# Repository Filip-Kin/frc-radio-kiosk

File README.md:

# FRC radio kiosk

Bench box that powers and configures FRC radios: dual-mode PoE (802.3at via
LTC4279, passive 12 V via TPS26600), USB-C PD or DC in, 15.6 V out for the
Toughbook, 4x CR123A backup, STM32F072 firmware.

- `Radio_Kiosk_v2/` first full board, 100 x 130 mm
- `Radio_Kiosk_v2b/` hand-packed board, 84 x 133 mm, 2 oz copper (order that at JLC)
- `Radio_Kiosk_v2d/` 4-layer rework of v2c, 85 x 120 mm, In1 GND plane (see its NOTES.md)
- `Radio_Kiosk_v1/` the built board, 70 x 105 mm: USB-C PD 20 V in, XL4015 16 V laptop out, LM2596 12 V passive PoE. Board was drawn in EasyEDA Pro; `fab/` is its 2026-03-25 export (Gerbers, BOM, STEP, 3D shell). The KiCad schematic is an early draft, not the built circuit.
- each board dir: `board.kicad_sch`, `board.kicad_pcb`, `board.kicad_pro`, `board.loon.json`, `firmware/` (PlatformIO)

The schematic and board are generated by scripts in
[loon](https://github.com/Filip-Kin/loon): `scripts/build-radio-kiosk.ts`,
`build-radio-kiosk-pcb.ts` (v2), `build-radio-kiosk-pcb-v2b.ts`. Design notes
are on the internal wiki (`frc/radio-kiosk-pcb`).

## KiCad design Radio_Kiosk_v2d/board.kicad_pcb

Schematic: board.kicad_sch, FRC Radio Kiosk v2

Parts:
BT1, BT2, BT3, BT4: CR123A; BAT-TH_BH-123A-A5BJ002; LCSC C5290177
C1, C2, C6, C7, C12, C13, C16, C17, C33, C48, C53, C99, C110, C111, C112, C114, C115, C116, C120, C131, C132, C133, C136: 100n; C_0805_2012Metric; LCSC C28233
C3, C5: 100n/50V; C_0805_2012Metric; LCSC C49678
C4: 47u/63V; CP_Elec_8x10.5; LCSC C970680
C8, C61, C140: 1u/50V; C_1206_3216Metric; LCSC C1848
C14, C15, C113, C135: 10n; C_0805_2012Metric; LCSC C1710
C20: 100p; C_0805_2012Metric; LCSC C1790
C21, C60, C119: 47n; C_0805_2012Metric; LCSC C53134
C22: 10u/25V; C_1210_3225Metric; LCSC C53084452
C23, C24, C26: 4.7u/100V; C_1210_3225Metric; LCSC C337978
C25: 47u/100V; CP_Elec_10x10.5; LCSC C970681
C30, C40, C44, C50, C90, C91: 10u/50V; C_1210_3225Metric; LCSC C53084452
C31, C41, C51: 220n/50V; C_0805_2012Metric; LCSC C5378
C32, C52, C118, C134: 1u; C_0805_2012Metric; LCSC C28323
C34, C35, C36, C37, C45, C54, C55, C56, C57: 22u/25V; C_1210_3225Metric; LCSC C53084530
C42: 4.7u/16V; C_0805_2012Metric; LCSC C1779
C43: 470n/16V; C_0805_2012Metric; LCSC C13967
C46: 220u/25V polymer; CP_Elec_6.3x7.7; LCSC C2981459
C49: 2.2n; C_0805_2012Metric; LCSC C28260
C62, C70: 1u/100V; C_1210_3225Metric; LCSC C24365
C71: 220n/100V; C_1210_3225Metric; LCSC C72067
C97, C98: 470u/25V; CP_Elec_10x10.5; LCSC C346948
C117: 4.7n; C_0805_2012Metric; LCSC C1744
C130: 4.7u; C_0805_2012Metric; LCSC C1779
C141: 1u; C_0603_1608Metric; LCSC C15849
C142, C143: 10u; C_0603_1608Metric; LCSC C19702
D1: SMAJ22A TVS; D_SMA; LCSC C148220
D2: SMAJ28A TVS; D_SMA; LCSC C148227
D20: SS310 100V Schottky; D_SMA; LCSC C15874
D21, D40: 1N4148W; D_SOD-123; LCSC C81598
D22, D70: SMAJ58A TVS; D_SMA; LCSC C10762
D23, D24: BZT52C12 zener; D_SOD-123; LCSC C12747
D30: WS2812B-4020 power LED; LED-SMD_WS2812B-4020; LCSC C965557
D31: WS2812B-4020 radio LED; LED-SMD_WS2812B-4020; LCSC C965557
D32: SS14 flyback; D_SMA; LCSC C2480
D71: S1B clamp; D_SMA; LCSC C96324
F1: 2A; Fuse_1206_3216Metric; LCSC C2838912
J1: USB-C PD in; USB-C_TYPE-C-31-M-12; LCSC C165948
J2: DC in 18-26V, PJ-002BH 5.5x2.5; DC-IN-TH_PJ-002BH; LCSC C22359705
J3: Laptop out 15.6V, PJ-002BH 5.5x2.5 (v1 jack); DC-IN-TH_PJ-002BH; LCSC C22359705
J5: RJ45 radio; RJ45-TH_R-RJ45R08P-A004; LCSC C385834
J6: RJ45 laptop; RJ45-TH_R-RJ45R08P-A004; LCSC C385834
J8: Fan 12V; CONN-TH_XH-2A; LCSC C20079
J9: SWD; PinHeader_1x04_P2.54mm_Vertical
J11: UART; PinHeader_1x04_P2.54mm_Vertical
J12: USB-C; USB_C_Receptacle_HRO_TYPE-C-31-M-12; LCSC C165948
J13: Lid LEDs; CONN-TH_XH-3A; LCSC C2316
L3, L4: MDA1040-150M 15u 6A; IND-SMD_L10.0-W10.0-APS10A40M470; LCSC C2847554
L5: SRP7028A-100M 10u 3.5A; L_Bourns_SRP7028A_7.3x6.6mm; LCSC C2687402
L20: MDA1365-330M 33u 9A; L_12x12mm_H8mm; LCSC C2847586
Q1, Q2, Q6, Q7, Q12: SI4470EY; SOIC-8_3.9x4.9mm_P1.27mm; LCSC C7568913
Q8: AOD4185; TO-252-2; LCSC C400894
Q9, Q10, Q25, Q45: 2N7002; SOT-23; LCSC C8545
Q11, Q30: AO3400A; SOT-23; LCSC C20917
Q13, Q20: AO4482; SOIC-8_3.9x4.9mm_P1.27mm; LCSC C192576
Q22: PSMN075-100MSEX; LFPAK33; LCSC C478016
Q23: DMP10H400SE; SOT-223_L6.5-W3.5-P2.30-LS7.0-BR; LCSC C156277
Q24: BSS123; SOT-23; LCSC C78755
Q40, Q41: AOD4184A; TO-252-2; LCSC C99124
Q44: SI4401DDY; SOIC-8_3.9x4.9mm_P1.27mm; LCSC C72317
R5, R6, R29, R42, R80, R89, R92, R97, R100, R101: 100k; R_0805_2012Metric; LCSC C149504
R7, R9, R24, R26, R27, R46, R47, R49, R61, R62, R63, R66, R78, R79, R82, R83, R99, R105, R107, R111, R121: 10k; R_0805_2012Metric; LCSC C17414
R8, R21, R28, R48: 47k; R_0805_2012Metric; LCSC C17713
R10, R31: 20k; R_0805_2012Metric; LCSC C4328
R20: 15m 1W; R_2512_6332Metric; LCSC C44883
R22: 499k 1%; R_0805_2012Metric; LCSC C17721
R23, R50: 12k; R_0805_2012Metric; LCSC C17444
R25, R81: 1k; R_0805_2012Metric; LCSC C17513
R30: 220k; R_0805_2012Metric; LCSC C17556
R40: 2k; R_0805_2012Metric; LCSC C17604
R41, R65: 51k; R_0805_2012Metric; LCSC C17737
R44: 820k; R_0805_2012Metric; LCSC C50136
R45: 750R; R_0805_2012Metric; LCSC C17818
R51: 3k; R_0805_2012Metric; LCSC C17661
R60: 5.6k; R_0805_2012Metric; LCSC C4382
R64, R86: 1M 1%; R_0805_2012Metric; LCSC C17514
R70: 10R; R_0805_2012Metric; LCSC C17415
R71: 200R; R_0805_2012Metric; LCSC C17540
R72: 0.1R 1% 2W; R_2512_6332Metric; LCSC C844904
R73: 3.3k; R_0805_2012Metric; LCSC C26010
R74, R75, R76, R77, R103, R106: 100R; R_0805_2012Metric; LCSC C17408
R84: 1M; R_0805_2012Metric; LCSC C17514
R85, R88: 24R 2W pulse; R_2512_6332Metric; LCSC C25476
R87: 150k; R_0805_2012Metric; LCSC C17470
R90, R94: 33k; R_0805_2012Metric; LCSC C17633
R91, R95, R98: 4.7k; R_0805_2012Metric; LCSC C17673
R93, R96: 20m 1W; R_2512_6332Metric; LCSC C2885416
R104: 1R; R_0805_2012Metric; LCSC C25271
R112: 0R; R_0805_2012Metric; LCSC C17477
R113: 220R; R_0805_2012Metric; LCSC C17557
R120: 120k 1%; R_0805_2012Metric; LCSC C17436
R122, R123: 5.1k; R_0603_1608Metric; LCSC C23186
RT1: 10k NTC; R_0603_1608Metric; LCSC C13564
SW1: RESET; SW_SPST_B3U-1000P; LCSC C231329
SW2: BOOT0 (DFU); SW_SPST_B3U-1000P; LCSC C231329
U1, U2, U6, U7, U12: LM74700-Q1; SOT-23-6; LCSC C2941042
U3: LMR33630 12V; SOIC-8-1EP_3.9x4.9mm_P1.27mm_EP2.29x3mm; LCSC C841384
U4: LM3150 15.75V 4.5A; HTSSOP-14_L5.0-W4.4-P0.65-LS6.4-BL-EP; LCSC C48112
U5: LMR33630 5V; SOIC-8-1EP_3.9x4.9mm_P1.27mm_EP2.29x3mm; LCSC C841384
U10, U45: TLV7011; SOT-23-5; LCSC C702117
U20: LM3478 54V boost; SOIC-8_3.9x4.9mm_P1.27mm; LCSC C115907
U21: TPS26600 eFuse; HTSSOP-16-1EP_4.4x5mm_P0.65mm_EP3.4x5mm; LCSC C544399
U22: LTC4279; SOIC-16_3.9x9.9mm_P1.27mm; LCSC C687935
U30, U31: SN74AHCT1G125; SOT-23-5; LCSC C7484
U40: STM32F072CBT6; LQFP-48_7x7mm_P0.5mm; LCSC C81720
U41, U42: INA180A1; SOT-23-5; LCSC C122228
U43: MCP6001T-I/OT; SOT-23-5; LCSC C116490
U50: CH224A; ESSOP-10_CH224A; LCSC C42459160
U51: AP2112K-3.3; SOT-23-5; LCSC C51118
U52: USBLC6-2SC6; SOT-23-6; LCSC C7519

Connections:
+3V3: C17.1, C99.1, C115.1, C116.1, C120.1, C130.1, C131.1, C132.1, C133.1, C142.1, J9.3, J11.3, R26.1, R62.1, R79.1, R82.1, R107.1, R112.1, R121.1, SW2.2, U10.5 (VCC), U40.1 (VBAT), U40.24 (VDD), U40.36 (VDDIO2), U40.48 (VDD), U41.5 (VS), U42.5 (VS), U43.5 (VDD), U45.5 (VCC), U51.5 (VOUT)
+5V: C16.1, C54.1, C55.1, C56.1, C57.1, C110.1, C111.1, C112.1, C141.1, D30.2 (VDD), D31.2 (VDD), J13.1 (5V), L5.2, R50.1, U30.5 (VCC), U31.5 (VCC), U51.1 (VIN), U51.3 (EN)
+12V: C22.1, C50.1, C51.1, C61.1, C97.1, C98.1, D32.1 (K), J8.1, L20.1, Q6.5 (D), Q6.6 (D), Q6.7 (D), Q6.8 (D), Q8.2 (D), U5.2 (VIN), U5.3 (EN), U6.4 (CATHODE), U20.8 (VIN), U21.1 (IN), U21.2 (IN), U21.3 (UVLO)
+12V_BUCK: C6.2, C34.1, C35.1, C36.1, C37.1, L3.2, Q6.1 (S), Q6.2 (S), Q6.3 (S), R30.1, U6.3 (EN), U6.6 (ANODE)
+15V6_BUCK: C45.1, C46.1, C49.1, L4.2, R41.1, R96.1, U42.3 (IN+)
+15V6_S: C5.1, C7.2, Q7.1 (S), Q7.2 (S), Q7.3 (S), Q44.5 (D), Q44.6 (D), Q44.7 (D), Q44.8 (D), R96.2, U7.3 (EN), U7.6 (ANODE), U42.4 (IN-)
BK_ARM: Q9.2 (S), Q10.3 (D)
BK_DRV: Q9.1 (G), R81.2
BK_EN: Q10.1 (G), R89.1, U12.3 (EN), U40.5 (PF0/OSC_IN)
BK_GATE: Q8.1 (G), Q9.3 (D), R80.2
BK_MID: Q8.3 (S), Q12.5 (D), Q12.6 (D), Q12.7 (D), Q12.8 (D), R80.1, R85.1, R86.1, R88.1, U12.4 (CATHODE)
BK_ON: R81.1, R84.1, U10.1 (OUT), U40.6 (PF1/OSC_OUT)
BK_REF: R82.2, R83.1, R84.2, U10.3 (IN+)
BOOST_COMP: R24.1, U20.2 (COMP)
BOOST_COMPC: C21.1, R24.2
BOOST_CS: Q20.1 (S), Q20.2 (S), Q20.3 (S), R20.1, U20.1 (ISEN)
BOOST_DR: Q20.4 (G), U20.6 (DR)
BOOST_FA: D21.1 (K), R21.1, U20.7 (FA/SD)
BOOST_FB: C20.1, R22.2, R23.1, U20.3 (FB)
BOOST_OUT: C23.1, C24.1, C25.1, C26.1, D20.1 (K), D23.1 (K), Q23.3 (S), R22.1, R27.1, R42.1
BOOST_SD: R25.1, R26.2, U40.27 (PB14)
BOOST_SDD: D21.2 (A), R25.2
BOOST_SW: D20.2 (A), L20.2, Q20.5 (D), Q20.6 (D), Q20.7 (D), Q20.8 (D)
BYP_D: Q45.3 (D), R8.2
BYP_EN: Q45.1 (G), U45.1 (OUT)
BYP_G: D24.2 (A), Q44.4 (G), R7.2, R8.1
BYP_REF: R9.2, R10.1, U45.3 (IN+)
CC1: J12.A5 (CC1), R122.1
CC2: J12.B5 (CC2), R123.1
DCIN_SENSE: R94.2, R95.1, U40.19 (PB1/ADC9)
ETH_1: J5.1, J6.1
ETH_2: J5.2, J6.2
ETH_3: J5.3, J6.3
ETH_6: J5.6, J6.6
FAN_G: Q30.1 (G), R101.1, R106.2
FAN_N: D32.2 (A), J8.2, Q30.3 (D)
FAN_PWM: R106.1, U40.40 (PB4)
FAN_SENSE: C113.1, R105.2, U40.18 (PB0/ADC8)
FAN_SHUNT: Q30.2 (S), R104.1, R105.1
GND: BT4.2 (-), C3.2, C4.2, C5.2, C8.2, C13.2, C14.2, C15.2, C16.2, C17.2, C20.2, C21.2, C22.2, C23.2, C24.2, C25.2, C26.2, C30.2, C31.2, C32.2, C34.2, C35.2, C36.2, C37.2, C40.2, C41.2, C42.2, C44.2, C45.2, C46.2, C48.2, C50.2, C51.2, C52.2, C54.2, C55.2, C56.2, C57.2, C60.2, C61.2, C62.2, C70.2, C90.2, C91.2, C97.2, C98.2, C99.2, C110.2, C111.2, C112.2, C113.2, C114.2, C115.2, C116.2, C118.2, C119.2, C120.2, C130.2, C131.2, C132.2, C133.2, C134.2, C135.2, C136.2, C140.2, C141.2, C142.2, C143.2, D1.2 (A), D2.2 (A), D22.2 (A), D30.4 (VSS), D31.4 (VSS), D70.2 (A), J1.1 (SHELL), J1.2 (SHELL), J1.3 (SHELL), J1.4 (SHELL), J1.A1B12 (GND), J1.B1A12 (GND), J2.2 (GND), J3.2 (GND), J9.4, J11.4, J12.A1 (GND), J12.A12, J12.B1 (GND2), J12.B12, J12.S1 (SHIELD), J13.3 (GND), Q10.2 (S), Q11.2 (S), Q13.1 (S), Q13.2 (S), Q13.3 (S), Q24.2 (S), Q25.2 (S), Q41.3 (S), Q45.2 (S), R6.2, R10.2, R20.2, R21.2, R23.2, R29.2, R31.2, R40.2, R42.2, R49.2, R51.2, R60.2, R61.2, R63.2, R65.2, R66.2, R72.2, R73.2, R74.2, R75.2, R76.2, R78.2, R83.2, R87.2, R89.2, R91.2, R92.2, R95.2, R100.2, R101.2, R104.2, R111.2, R120.2, R122.2, R123.2, RT1.2, SW1.2, U1.2 (GND), U2.2 (GND), U3.1 (PGND), U3.9 (AGND), U4.5 (SGND), U4.9 (SGND), U4.14 (PGND), U4.15 (EP), U5.1 (PGND), U5.9 (AGND), U6.2 (GND), U7.2 (GND), U10.2 (VEE), U12.2 (GND), U20.4 (AGND), U20.5 (PGND), U21.5 (OVP), U21.8 (RTN), U21.9 (GND), U21.17 (PAD), U22.4 (VSSK), U22.10 (VEE), U30.1 (OE), U30.3 (GND), U31.1 (OE), U31.3 (GND), U40.8 (VSSA), U40.23 (VSS), U40.35 (VSS), U40.47 (VSS), U41.2 (GND), U42.2 (GND), U43.2 (VSS), U45.2 (VEE), U50.11 (EPAD), U51.2 (GND), U52.2 (GND)
LAPTOP_BYP: R9.1, U40.20 (PB2)
LAPTOP_CC: C117.1, D40.2 (A), U43.1 (OUT)
LAPTOP_CC_D: D40.1 (K), R98.1
LAPTOP_EN: R46.1, U40.46 (PB9)
LAPTOP_ILIM: C118.1, R97.1, R99.2
LAPTOP_ILIM_N: C117.2, R97.2, U43.4 (IN-)
LAPTOP_ILIM_PWM: R99.1, U40.29 (PA8/TIM1_CH1)
LAPTOP_ISENSE: R47.1, U40.14 (PA4/ADC4), U42.1 (OUT)
LAPTOP_ISENSE_F: C119.1, R47.2, U43.3 (IN+)
LAPTOP_OK: R48.2, R49.1, U40.2 (PC13)
LAPTOP_OUT: C8.1, J3.1 (V+), Q7.5 (D), Q7.6 (D), Q7.7 (D), Q7.8 (D), R48.1, U7.4 (CATHODE)
LED_D0: R103.1, U30.4 (Y)
LED_D0R: D30.1 (DIN), R103.2
LED_D1: D30.3 (DOUT), D31.1 (DIN)
LED_D2: D31.3 (DOUT), R113.1
LED_D2W: J13.2 (DATA), R113.2
LED_DATA: U30.2 (A), U40.45 (PB8)
MCU_BOOT0: R111.1, SW2.1, U40.44 (BOOT0)
MCU_NRST: C136.1, SW1.1, U40.7 (NRST)
MCU_VDDA: C134.1, C135.1, R112.2, U40.9 (VDDA)
PACK_1: BT1.2 (-), BT2.1 (+)
PACK_2: BT2.2 (-), BT3.1 (+)
PACK_3: BT3.2 (-), BT4.1 (+)
PACK_F: C12.2, F1.2 (OUT), Q12.1 (S), Q12.2 (S), Q12.3 (S), U12.6 (ANODE)
PACK_P: BT1.1 (+), F1.1 (IN)
PACK_SENSE: C13.1, R86.2, R87.1, U40.12 (PA2/ADC2)
PASSIVE_DVDT: C60.1, U21.12 (dVdT)
PASSIVE_EN: R63.1, U21.7 (SHDN), U31.2 (A), U40.21 (PB10)
PASSIVE_EN5: Q13.4 (G), R66.1, U31.4 (Y)
PASSIVE_FLT: R62.2, U21.14 (FLT), U40.25 (PB12)
PASSIVE_ILIM: R60.1, U21.11 (ILIM)
PASSIVE_IMON: R61.1, U21.10 (IMON), U40.15 (PA5/ADC5)
PD_CC1: J1.A5 (CC1), U50.7 (CC1)
PD_CC2: J1.B5 (CC2), U50.6 (CC2)
PD_CFG1: R120.1, U50.9 (CFG1)
PD_DM: J1.A7 (D-), J1.B7 (D-2), U50.5 (DM)
PD_DP: J1.A6 (D+), J1.B6 (D+2), U50.4 (DP)
PD_PG: R121.2, U40.31 (PA10), U50.10 (PG)
PD_SCL: U40.38 (PA15), U50.2 (CFG2/SCL)
PD_SDA: U40.39 (PB3), U50.3 (CFG3/SDA)
PORT_N: C71.1, D71.2 (A), J5.7, J5.8, Q13.5 (D), Q13.6 (D), Q13.7 (D), Q13.8 (D), Q22.5 (D), U22.7 (OUT)
PORT_P: C62.1, D22.1 (K), D71.1 (K), J5.4, J5.5, Q23.2 (D), Q23.4 (D), R64.1, R70.1, U21.15 (OUT), U21.16 (OUT)
PORT_SENSE: C15.1, R64.2, R65.1, U40.17 (PA7/ADC7)
PORT_SW: Q24.1 (G), R29.1, U40.4 (PC15/OSC32_OUT)
PORT_SW_D: Q24.3 (D), R28.2
PORT_SW_G: D23.2 (A), Q23.1 (G), R27.2, R28.1
PSE_AGND: C70.1, C71.2, D70.1 (K), R70.2, U22.8 (AGND)
PSE_DUALPD: R76.1, U22.14 (DUALPD)
PSE_EN: R77.1, U40.26 (PB13)
PSE_GATE: Q22.4 (G), R71.2
PSE_GATE_DRV: R71.1, U22.6 (GATE)
PSE_LEGACY: R75.1, U22.13 (LEGACY)
PSE_MID: R74.1, U22.1 (MID)
PSE_ON: R79.2, U22.9 (LED), U40.22 (PB11)
PSE_PWRMODE: R73.1, U22.12 (PWRMODE)
PSE_RESET: R77.2, R78.1, U22.16 (RESET)
PSE_SENSE: Q22.1 (S), Q22.2 (S), Q22.3 (S), R72.1, U22.5 (SENSE)
SWCLK: J9.2, U40.37 (PA14/SWCLK)
SWDIO: J9.1, U40.34 (PA13/SWDIO)
TEMP_SENSE: C114.1, R107.2, RT1.1, U40.16 (PA6/ADC6/TIM3_CH1)
TEST_LOAD: Q11.1 (G), R100.1, U40.30 (PA9)
TEST_NODE: Q11.3 (D), R85.2, R88.2
U1_GATE: Q1.4 (G), U1.5 (GATE)
U1_VCAP: C1.1, U1.1 (VCAP)
U2_GATE: Q2.4 (G), U2.5 (GATE)
U2_VCAP: C2.1, U2.1 (VCAP)
U3_BOOT: C33.1, U3.7 (BOOT)
U3_FB: R30.2, R31.1, U3.5 (FB)
U3_SW: C33.2, L3.1, U3.8 (SW)
U3_VCC: C32.1, U3.6 (VCC)
U4_BST: C43.1, U4.12 (BST)
U4_EN: R46.2, R92.1, U4.3 (EN)
U4_FB: C49.2, R40.1, R41.2, R98.2, U4.4 (FB)
U4_HG: Q40.1 (G), U4.11 (HG)
U4_ILIM: R45.1, U4.8 (ILIM)
U4_LG: Q41.1 (G), U4.13 (LG)
U4_RON: R44.2, U4.7 (RON)
U4_SS: C48.1, U4.6 (SS)
U4_SW: C43.2, L4.1, Q40.3 (S), Q41.2 (D), R45.2, U4.10 (SW)
U4_VCC: C42.1, U4.1 (VCC)
U5_BOOT: C53.1, U5.7 (BOOT)
U5_FB: R50.2, R51.1, U5.5 (FB)
U5_SW: C53.2, L5.1, U5.8 (SW)
U5_VCC: C52.1, U5.6 (VCC)
U6_GATE: Q6.4 (G), U6.5 (GATE)
U6_VCAP: C6.1, U6.1 (VCAP)
U7_GATE: Q7.4 (G), U7.5 (GATE)
U7_VCAP: C7.1, U7.1 (VCAP)
U12_GATE: Q12.4 (G), U12.5 (GATE)
U12_VCAP: C12.1, U12.1 (VCAP)
UART_RX: J11.2, U40.43 (PB7)
UART_TX: J11.1, U40.42 (PB6)
USB_D+: U40.33 (PA12/USB_DP), U52.4 (I/O2_OUT)
USB_D-: U40.32 (PA11/USB_DM), U52.6 (I/O1_OUT)
USB_DIS: Q25.1 (G), R6.1, U40.41 (PB5)
USB_DM_CON: J12.A7 (D-), J12.B7 (D-2), U52.1 (I/O1)
USB_DP_CON: J12.A6 (D+), J12.B6 (D+2), U52.3 (I/O2)
USB_EN: Q25.3 (D), R5.2, U1.3 (EN)
USB_ISENSE: U40.13 (PA3/ADC3), U41.1 (OUT)
USB_VBUS: C143.1, J12.A4 (VBUS), J12.A9, J12.B4 (VBUS2), J12.B9, U52.5 (VBUS)
VIN: C4.1, C30.1, C31.1, C40.1, C41.1, C44.1, C90.1, C91.1, D24.1 (K), Q1.5 (D), Q1.6 (D), Q1.7 (D), Q1.8 (D), Q2.5 (D), Q2.6 (D), Q2.7 (D), Q2.8 (D), Q40.2 (D), Q44.1 (S), Q44.2 (S), Q44.3 (S), R7.1, R44.1, R90.1, U1.4 (CATHODE), U2.4 (CATHODE), U3.2 (VIN), U3.3 (EN), U4.2 (VIN)
VIN_DC: C2.2, C3.1, D2.1 (K), J2.1 (V+), Q2.1 (S), Q2.2 (S), Q2.3 (S), R94.1, U2.3 (EN), U2.6 (ANODE)
VIN_SENSE: C14.1, R90.2, R91.1, U10.4 (IN-), U40.11 (PA1/ADC1), U45.4 (IN-)
VIN_USB: C140.1, D1.1 (K), J1.A4B9 (VBUS), J1.B4A9 (VBUS), R93.1, U41.3 (IN+), U50.1 (VHV), U50.8 (VBUS)
VIN_USBS: C1.2, Q1.1 (S), Q1.2 (S), Q1.3 (S), R5.1, R93.2, U1.6 (ANODE), U41.4 (IN-)

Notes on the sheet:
STAGES 1-3 DONE: power tree, radio port, MCU. Stage 4 = the board. Port placement for the board: TOP edge = laptop side (J6 RJ45 laptop, J3 laptop DC out, the USB-C serial). RIGHT edge = power in (J1 PD trigger module, J2 DC jack). BOTTOM edge = radio (J5 RJ45 radio). D30 sits by the power inputs, 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
RADIO PORT: PORT_P = pins 4/5, PORT_N = pins 7/8 (Mode B). Unknown port: boost on, Q23 (PORT_SW) closed, PSE_EN: U22 probes the PD. Valid 802.3 signature within 700 ms: active, U22 powers PORT_N, 54 V on the port. No signature: PORT_SW open, PSE_EN off, PORT_P decays through R64, then PASSIVE_EN: U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
PSE: LTC4279 (SO-16) per datasheet Figure 13. PORT_P is its AGND supply through R70 10R; board GND is its VEE; Q22 (PSMN075-100MSEX, ADI's recommended FET) switches PORT_N through R72 0.1R. PWRMODE 3.32k = Type 2, 25.5 W. RESET pulled down: port off until the MCU raises PSE_EN. PSE_ON is low while 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
INPUTS: 14-26 V from a USB-C PD trigger module (J1) or a DC jack (J2), ideal-diode ORed. Highest wins. The USB-C PD sink (CH224A) is on the board now, no trigger module. Standard supply is a 24 V 5 A brick; the Toughbook's own 15.6 V brick or a 19-20 V laptop brick also work. J2 and J3 are both 5.5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
RAILS: +12V is the backed-up rail (radio passive output, 54 V PSE boost, 5 V, 3.3 V). LAPTOP_OUT is off the raw input so it sheds itself on a dropout. Bucks are LMR33630 at 400 kHz per datasheet Table 9-1; the laptop one is set to 15.6 V (the Toughbook brick voltage) and runs in dropout on that bri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
BACKUP: 4x CR123A (12 V nominal, no boost, no BMS). Q8 closes when Vin < 16 V, opens when it returns. R84 hysteresis. Firmware (stage 3) opens it after 2 s of no radio load or 5 min, by pulling BK_ON low through a diode-OR at R81 (TBD stage 3). Self-test: TEST_LOAD high for 200 ms, read PACK_SENSE;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
ASSEMBLY: all SMT except connectors and cell holders, so the BOM is production-ready as is. First units hand-built: every IC is SO / SOT-23 / HTSSOP, passives 0805+, exposed pads (3 bucks, eFuse, FETs) get thermal vias for hot air. No leadless packages.
OPEN: Passive-mode radio draw (assumed 10 W) and the PD brick's dropout time still need measuring. Laptop rail is off at reset (LAPTOP_EN) and constant-current limited (LAPTOP_ILIM): firmware sets the limit to allocation minus the box draw so a shared charger never trips; what the Toughbook does wh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
MCU: STM32F072CBT6 (128 KB), no radio. ADC: PA0 VIN_SENSE, PA1 PACK_SENSE (1M/150k), PA2 PASSIVE_IMON, PA3 TEMP_SENSE, PA4 FAN_SENSE, ADC5 USB_ISENSE (2 V = 5 A), ADC7 DCIN_SENSE, ADC8 PORT_SENSE (1M/51k, 56 V = 2.72 V), ADC9 LAPTOP_ISENSE (0.4 V = 1 A). Out: PB2 LAPTOP_EN (off at reset), PA9 LAPTO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

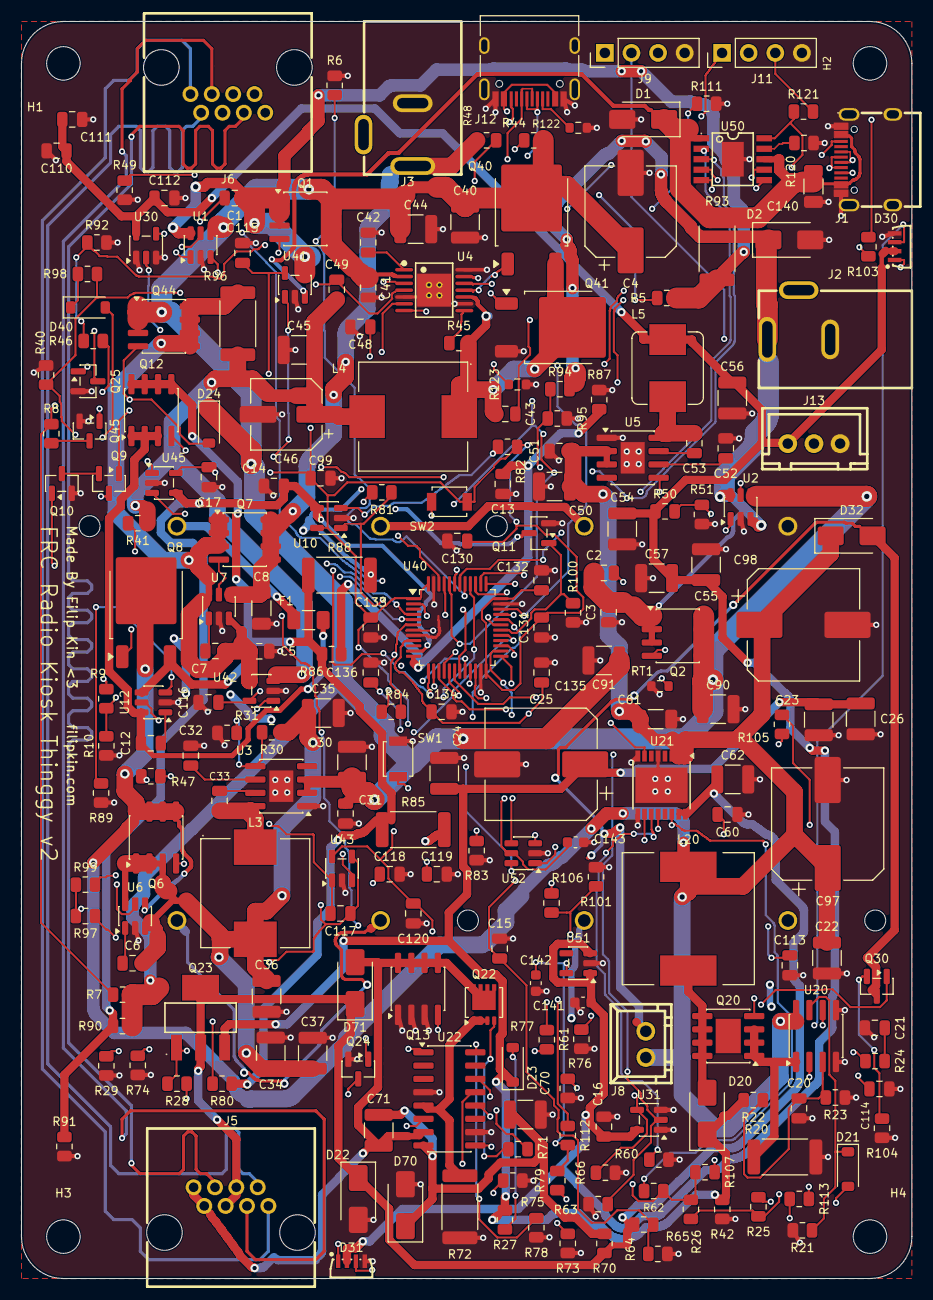
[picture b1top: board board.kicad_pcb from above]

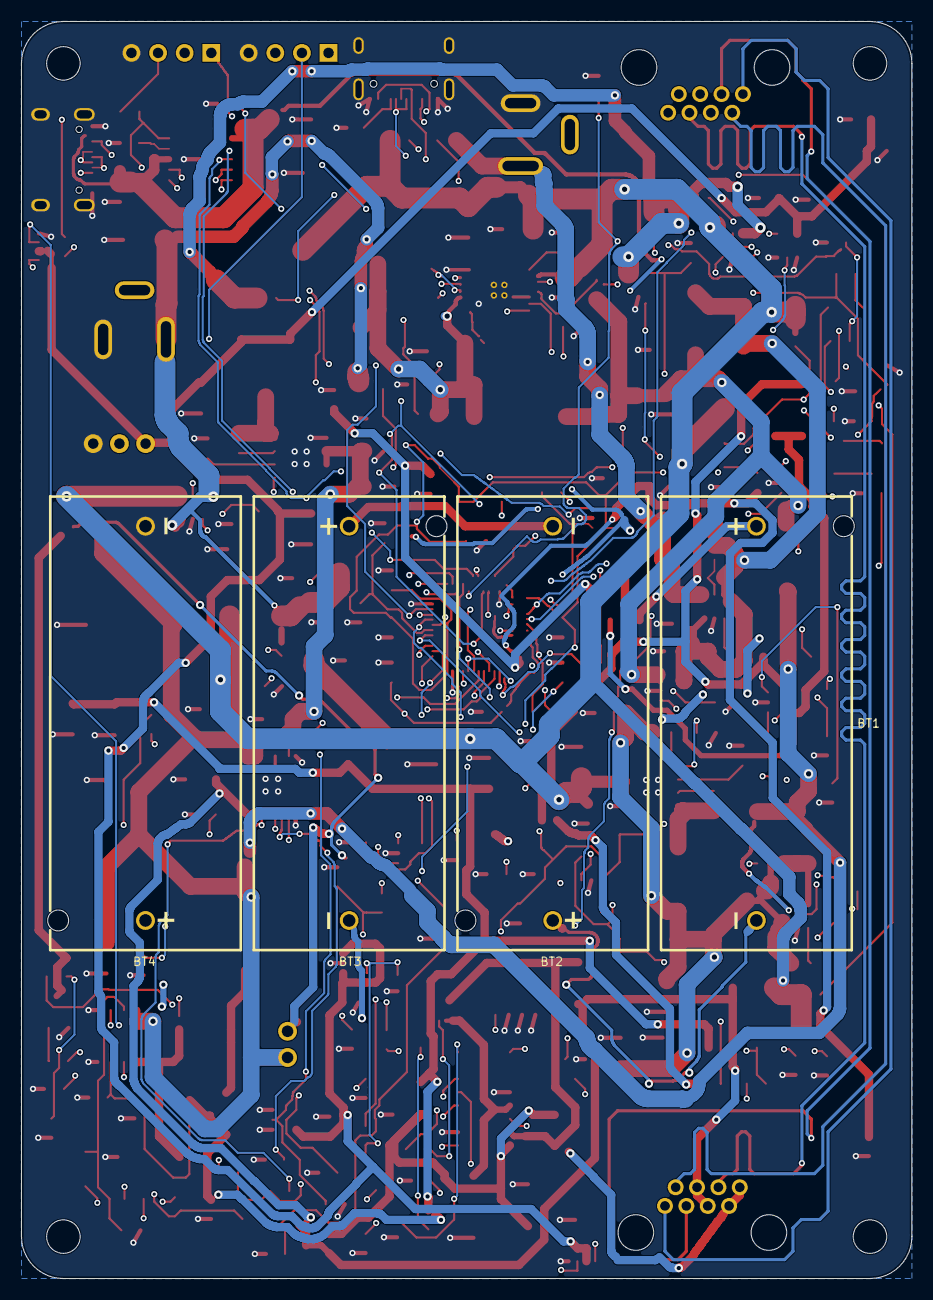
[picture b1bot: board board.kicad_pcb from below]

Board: 4 copper layers, 85.0 x 120.0 mm, 239 parts (4 on the bottom side), 145 nets.

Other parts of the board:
H1, H2, H3, H4: M3 mount; MountingHole_3.2mm_M3

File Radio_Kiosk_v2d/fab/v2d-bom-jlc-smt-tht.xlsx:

Comment | Designator | Footprint | LCSC Part #
100n | C1,C2,C6,C7,C12,C13,C16,C17,C33,C48,C53,C99,C110,C111,C112,C114,C115,C116,C120,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 | C_0805_2012Metric | C28233
100n/50V | C3,C5 | C_0805_2012Metric | C49678
47u/63V | C4 | CP_Elec_8x10.5 | C970680
1u/50V | C8,C61,C140 | C_1206_3216Metric | C1848
10n | C14,C15,C113,C135 | C_0805_2012Metric | C1710
100p | C20 | C_0805_2012Metric | C1790
47n | C21,C60,C119 | C_0805_2012Metric | C53134
10u/25V | C22 | C_1210_3225Metric | C53084452
4.7u/100V | C23,C24,C26 | C_1210_3225Metric | C337978
47u/100V | C25 | CP_Elec_10x10.5 | C970681
10u/50V | C30,C40,C50,C90,C91,C44 | C_1210_3225Metric | C53084452
220n/50V | C31,C41,C51 | C_0805_2012Metric | C5378
1u | C32,C52,C118,C134 | C_0805_2012Metric | C28323
22u/25V | C34,C35,C36,C37,C45,C54,C55,C56,C57 | C_1210_3225Metric | C53084530
4.7u/16V | C42 | C_0805_2012Metric | C1779
470n/16V | C43 | C_0805_2012Metric | C13967
220u/25V polymer | C46 | CP_Elec_6.3x7.7 | C2981459
2.2n | C49 | C_0805_2012Metric | C28260
1u/100V | C62,C70 | C_1210_3225Metric | C24365
220n/100V | C71 | C_1210_3225Metric | C72067
470u/25V | C97,C98 | CP_Elec_10x10.5 | C346948
4.7n | C117 | C_0805_2012Metric | C1744
4.7u | C130 | C_0805_2012Metric | C1779
1u | C141 | C_0603_1608Metric | C15849
10u | C142,C143 | C_0603_1608Metric | C19702
SMAJ22A TVS | D1 | D_SMA | C148220
SMAJ28A TVS | D2 | D_SMA | C148227
SS310 100V Schottky | D20 | D_SMA | C15874
1N4148W | D21,D40 | D_SOD-123 | C81598
SMAJ58A TVS | D22,D70 | D_SMA | C10762
BZT52C12 zener | D23,D24 | D_SOD-123 | C12747
WS2812B-4020 power LED | D30 | LED-SMD_WS2812B-4020 | C965557
WS2812B-4020 radio LED | D31 | LED-SMD_WS2812B-4020 | C965557
SS14 flyback | D32 | D_SMA | C2480
S1B clamp | D71 | D_SMA | C96324
2A | F1 | Fuse_1206_3216Metric | C2838912
USB-C PD in | J1 | USB-C_TYPE-C-31-M-12 | C165948
DC in 18-26V, PJ-002BH 5.5x2.5 | J2 | DC-IN-TH_PJ-002BH | C22359705
Laptop out 15.6V, PJ-002BH 5.5x2.5 (v1 jack) | J3 | DC-IN-TH_PJ-002BH | C22359705
RJ45 radio | J5 | RJ45-TH_R-RJ45R08P-A004 | C385834
RJ45 laptop | J6 | RJ45-TH_R-RJ45R08P-A004 | C385834
Fan 12V | J8 | CONN-TH_XH-2A | C20079
USB-C | J12 | USB_C_Receptacle_HRO_TYPE-C-31-M-12 | C165948
Lid LEDs | J13 | CONN-TH_XH-3A | C2316
MDA1040-150M 15u 6A | L3,L4 | IND-SMD_L10.0-W10.0-APS10A40M470 | C2847554
SRP7028A-100M 10u 3.5A | L5 | L_Bourns_SRP7028A_7.3x6.6mm | C2687402
MDA1365-330M 33u 9A | L20 | L_12x12mm_H8mm | C2847586
SI4470EY | Q1,Q2,Q6,Q7,Q12 | SOIC-8_3.9x4.9mm_P1.27mm | C7568913
AOD4185 | Q8 | TO-252-2 | C400894
2N7002 | Q9,Q10,Q25,Q45 | SOT-23 | C8545
AO3400A | Q11,Q30 | SOT-23 | C20917
AO4482 | Q13,Q20 | SOIC-8_3.9x4.9mm_P1.27mm | C192576
PSMN075-100MSEX | Q22 | LFPAK33 | C478016
DMP10H400SE | Q23 | SOT-223_L6.5-W3.5-P2.30-LS7.0-BR | C156277
BSS123 | Q24 | SOT-23 | C78755
AOD4184A | Q40,Q41 | TO-252-2 | C99124
SI4401DDY | Q44 | SOIC-8_3.9x4.9mm_P1.27mm | C72317
100k | R5,R6,R29,R42,R80,R89,R92,R97,R100,R101 | R_0805_2012Metric | C149504
10k | R7,R9,R24,R26,R27,R46,R47,R49,R61,R62,R63,R66,R78,R79,R82,R83,R99,R105,R107,R11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 | R_0805_2012Metric | C17414
47k | R8,R21,R28,R48 | R_0805_2012Metric | C17713
20k | R10,R31 | R_0805_2012Metric | C4328
15m 1W | R20 | R_2512_6332Metric | C44883
499k 1% | R22 | R_0805_2012Metric | C17721
12k | R23,R50 | R_0805_2012Metric | C17444
1k | R25,R81 | R_0805_2012Metric | C17513
220k | R30 | R_0805_2012Metric | C17556
2k | R40 | R_0805_2012Metric | C17604
51k | R41,R65 | R_0805_2012Metric | C17737
820k | R44 | R_0805_2012Metric | C50136
750R | R45 | R_0805_2012Metric | C17818
3k | R51 | R_0805_2012Metric | C17661
5.6k | R60 | R_0805_2012Metric | C4382
1M 1% | R64,R86 | R_0805_2012Metric | C17514
10R | R70 | R_0805_2012Metric | C17415
200R | R71 | R_0805_2012Metric | C17540
0.1R 1% 2W | R72 | R_2512_6332Metric | C844904
3.3k | R73 | R_0805_2012Metric | C26010
100R | R74,R75,R76,R77,R103,R106 | R_0805_2012Metric | C17408
1M | R84 | R_0805_2012Metric | C17514
24R 2W pulse | R85,R88 | R_2512_6332Metric | C25476
150k | R87 | R_0805_2012Metric | C17470
33k | R90,R94 | R_0805_2012Metric | C17633
4.7k | R91,R95,R98 | R_0805_2012Metric | C17673
20m 1W | R93,R96 | R_2512_6332Metric | C2885416
1R | R104 | R_0805_2012Metric | C25271
0R | R112 | R_0805_2012Metric | C17477
220R | R113 | R_0805_2012Metric | C17557
120k 1% | R120 | R_0805_2012Metric | C17436
5.1k | R122,R123 | R_0603_1608Metric | C23186
10k NTC | RT1 | R_0603_1608Metric | C13564
RESET | SW1 | SW_SPST_B3U-1000P | C231329
BOOT0 (DFU) | SW2 | SW_SPST_B3U-1000P | C231329
LM74700-Q1 | U1,U2,U6,U7,U12 | SOT-23-6 | C2941042
LMR33630 12V | U3 | SOIC-8-1EP_3.9x4.9mm_P1.27mm_EP2.29x3mm | C841384
LM3150 15.75V 4.5A | U4 | HTSSOP-14_L5.0-W4.4-P0.65-LS6.4-BL-EP | C48112
LMR33630 5V | U5 | SOIC-8-1EP_3.9x4.9mm_P1.27mm_EP2.29x3mm | C841384
TLV7011 | U10,U45 | SOT-23-5 | C702117
LM3478 54V boost | U20 | SOIC-8_3.9x4.9mm_P1.27mm | C115907
TPS26600 eFuse | U21 | HTSSOP-16-1EP_4.4x5mm_P0.65mm_EP3.4x5mm | C544399
LTC4279 | U22 | SOIC-16_3.9x9.9mm_P1.27mm | C687935
SN74AHCT1G125 | U30,U31 | SOT-23-5 | C7484
STM32F072CBT6 | U40 | LQFP-48_7x7mm_P0.5mm | C81720
INA180A1 | U41,U42 | SOT-23-5 | C122228
MCP6001T-I/OT | U43 | SOT-23-5 | C116490
CH224A | U50 | ESSOP-10_CH224A | C42459160
AP2112K-3.3 | U51 | SOT-23-5 | C51118
USBLC6-2SC6 | U52 | SOT-23-6 | C7519

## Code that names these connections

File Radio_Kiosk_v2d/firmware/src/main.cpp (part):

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// registers directly.

// #region pins
static const int PIN_VIN_SENSE = PA1;      // 33k/4.7k: 1.65 V = 13.2 V
static const int PIN_PACK_SENSE = PA2;     // 1M/150k after the pack ideal diode
static const int PIN_PASSIVE_IMON = PA5;   // TPS26600 IMON into 10k: 0.78 V/A
static const int PIN_TEMP_SENSE = PA6;     // 10k / NTC 10k B3380 to GND
static const int PIN_FAN_SENSE = PB0;      // 1R shunt through 10k/10n
static const int PIN_USB_ISENSE = PA3;     // INA180A1 x20 on 20 mR: 0.4 V/A
static const int PIN_DCIN_SENSE = PB1;     // 33k/4.7k on the DC jack
static const int PIN_PORT_SENSE = PA7;     // 1M/51k on PORT_P: 20.6 V per volt
static const int PIN_LAPTOP_ISENSE = PA4;  // INA180A1 x20 on 20 mR: 0.4 V/A

static const int PIN_LAPTOP_EN = PB9;
static const int PIN_TEST_LOAD = PA9;
static const int PIN_BOOST_SD = PB14;      // high = boost off (pulled up at reset)
static const int PIN_PASSIVE_EN = PB10;
static const int PIN_PSE_EN = PB13;
static const int PIN_PORT_SW = PC15;       // high closes Q23: boost output onto the port
static const int PIN_USB_DIS = PB5;        // high drops the USB-C input path
static const int PIN_FAN_PWM = PB4;        // TIM3_CH1
static const int PIN_LED_DATA = PB8;       // through the AHCT buffer to two WS2812B-4020
static const int PIN_BK_EN = PF0;         // high arms the pack switch (and its ideal diode)
static const int PIN_LAPTOP_ILIM = PA8;    // TIM1_CH2, filtered: 0.4 V per amp of limit
static const int PIN_LAPTOP_BYP = PB2;    // high lets Q44 bypass the buck below ~17.6 V in

static const int PIN_BK_ON = PF1;          // comparator: high = on battery
static const int PIN_PASSIVE_FLT = PB12;    // eFuse fault, active low
static const int PIN_PSE_ON = PB11;         // LTC4279 LED pin, low = port powered
static const int PIN_PD_PG = PA10;          // CH224A PG, low = 20 V granted
static const int PIN_LAPTOP_OK = PC13;     // 47k/10k on LAPTOP_OUT: high above ~5.6 V

// J11 is USART1 on PB6/PB7. STM32duino defaults USART1 to PA9/PA10, which are
// LAPTOP_ILIM and BK_EN, so the pins are set before Serial1.begin().
static const int PIN_UART_TX = PB6;
static const int PIN_UART_RX = PB7;

// #region scaling
static const float ADC_V = 3.3f / 4095.0f;
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static float readV(int pin) { return analogRead(pin) * ADC_V; }

static void sampleAnalog() {
  vinV = readV(PIN_VIN_SENSE) * DIV_HV;
  packV = readV(PIN_PACK_SENSE) * DIV_PACK;
  dcinV = readV(PIN_DCIN_SENSE) * DIV_HV;
  portV = readV(PIN_PORT_SENSE) * DIV_PORT;
  passiveA = readV(PIN_PASSIVE_IMON) / 0.78f;
  usbA = readV(PIN_USB_ISENSE) / 0.4f;
  laptopA = readV(PIN_LAPTOP_ISENSE) / LAPTOP_V_PER_A;
  float vt = readV(PIN_TEMP_SENSE);
  tempFault = vt < 0.01f || vt > 3.29f;
  if (!tempFault) {
    float r = 10000.0f * vt / (3.3f - vt);
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  // A spinning fan puts commutation ripple on its shunt; a stalled one is flat.
  float lo = 9, hi = 0;
  for (int i = 0; i < 32; i++) {
    float v = readV(PIN_FAN_SENSE);
    lo = min(lo, v); hi = max(hi, v);
    delayMicroseconds(200);
  }
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static const char *portNote = "";

static void portAllOff() {
  digitalWrite(PIN_PSE_EN, LOW);
  digitalWrite(PIN_PORT_SW, LOW);
  digitalWrite(PIN_BOOST_SD, HIGH);
  digitalWrite(PIN_PASSIVE_EN, LOW);
}

static bool pseOn() { return digitalRead(PIN_PSE_ON) == LOW; }
static bool passiveFault() { return digitalRead(PIN_PASSIVE_FLT) == LOW; }

static void portGo(PortMode m, uint32_t now, const char *note = "") {
  port = m; portSince = now; probeStep = 0; portNote = note;
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      backfeed = portV > 0.15f;
      if (backfeed) { portNote = "backfeed on idle port"; break; }
      if (t < 300) break;   // let the port settle between windows
      if (activeAvail && activeEnabled) { digitalWrite(PIN_BOOST_SD, LOW); portGo(PORT_PROBE, now); }
      else { digitalWrite(PIN_PASSIVE_EN, HIGH); portGo(PORT_PASSIVE, now); }
      break;
    case PORT_PROBE:
      // 0: boost soft-start (4 ms typ). 1: port switch closed, wait for the
      // 54 V to reach the port. 2: PSE detecting; a valid signature powers the
      // port inside 570 ms worst case.
      if (probeStep == 0 && t > 10) { digitalWrite(PIN_PORT_SW, HIGH); probeStep = 1; }
      else if (probeStep == 1) {
        if (portV > 45.0f) { digitalWrite(PIN_PSE_EN, HIGH); probeStep = 2; portSince = now; }
        else if (t > 200) {
          // No boost voltage: the active parts are not on this board.
          activeAvail = false;
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      break;
    case PORT_TEARDOWN:
      // The LTC4279's own supply pulls PORT_P down once Q23 is open (tau ~26 ms).
      if (portV < 0.15f || t > 400) { digitalWrite(PIN_PASSIVE_EN, HIGH); portGo(PORT_PASSIVE, now, "passive"); }
      break;
    case PORT_ACTIVE: {
      // PSE_ON must stay high for 500 ms before the port counts as unpowered,
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static uint32_t lastSelfTest = 0;

static void batteryTick(uint32_t now) {
  bool bk = digitalRead(PIN_BK_ON) == HIGH;
  if (bk && !onBattery) { batterySince = now; noLoadSince = 0; }
  onBattery = bk;
  // Off battery: keep the switch armed so the comparator can close it the
  // instant the input goes.
  if (!bk) { batteryKilled = false; digitalWrite(PIN_BK_EN, HIGH); return; }
  if (batteryKilled) return;
  if (!radioLoaded()) { if (!noLoadSince) noLoadSince = now; } else noLoadSince = 0;
  // 5 s is longer than a full probe window, so a port restart on battery does
  // not drop the pack before the radio is powered again.
  bool cut = (noLoadSince && now - noLoadSince > 5000) || (now - batterySince > batteryCapMs);
  if (cut) { digitalWrite(PIN_BK_EN, LOW); batteryKilled = true; }
}

// Two 200 ms pulses into the 12R dump; the first wakes lithium primaries from
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static void selfTest(uint32_t now) {
  if (onBattery) return;
  for (int i = 0; i < 2; i++) {
    digitalWrite(PIN_TEST_LOAD, HIGH);
    delay(180);
    packLoadedV = readV(PIN_PACK_SENSE) * DIV_PACK;
    delay(20);
    digitalWrite(PIN_TEST_LOAD, LOW);
    delay(300);
  }
  packOk = packLoadedV > 8.8f;
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struct PdInfo { bool ok; uint8_t addr; uint8_t status; uint8_t currentReg; float maxA; };
static PdInfo pd = { false, 0x22, 0, 0, 0 };

// #region bit-banged I2C on PA15 (SCL) / PB3 (SDA), ~50 kHz, open-drain
// The CH224A is powered from the USB-C input. With no USB in, the pins stay
// plain inputs: pull-ups into an unpowered part would feed it through its
// protection diodes.
static const int PIN_SCL = PA15, PIN_SDA = PB3;
static inline void sclHi() { pinMode(PIN_SCL, INPUT_PULLUP); }
static inline void sclLo() { pinMode(PIN_SCL, OUTPUT); digitalWrite(PIN_SCL, LOW); }
static inline void sdaHi() { pinMode(PIN_SDA, INPUT_PULLUP); }
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  return ok;
}

static bool usbPresent() { return digitalRead(PIN_PD_PG) == LOW; }

static void pdTick() {
  if (!usbPresent()) { pd.ok = false; pd.maxA = 0; i2cRelease(); return; }
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}

// #region PWM on the timer registers
// Rev C: TIM3_CH1 on PB4 (AF1) for the fan at 25 kHz; TIM1_CH1 on PA8 (AF2)
// for the laptop current-limit setpoint at 20 kHz. Register level, no HAL.
static void pwmInit() {
  RCC->AHBENR |= RCC_AHBENR_GPIOAEN | RCC_AHBENR_GPIOBEN;
  RCC->APB1ENR |= RCC_APB1ENR_TIM3EN;
  RCC->APB2ENR |= RCC_APB2ENR_TIM1EN;
  // PB4 -> AF1 (TIM3_CH1), PA8 -> AF2 (TIM1_CH1)
  GPIOB->MODER = (GPIOB->MODER & ~(3u << (4 * 2))) | (2u << (4 * 2));
  GPIOB->AFR[0] = (GPIOB->AFR[0] & ~(0xFu << (4 * 4))) | (1u << (4 * 4));
  GPIOA->MODER = (GPIOA->MODER & ~(3u << (8 * 2))) | (2u << (8 * 2));
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  // Shorted jack: the CC loop would hold the buck in a happy 4.5 A short
  // forever, so watch the jack voltage. 200 ms low while enabled = fault,
  // retry after 5 s.
  bool jackOk = digitalRead(PIN_LAPTOP_OK) == HIGH;
  if ((laptopOn || laptopBypass) && !jackOk) { if (!laptopBadSince) laptopBadSince = now; }
  else laptopBadSince = 0;
  if (laptopBadSince && now - laptopBadSince > 200) { laptopFault = true; laptopFaultSince = now; laptopBadSince = 0; }
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  // sagging 20 V source does not flap.
  bool lowBrick = laptopBypass ? vinV < 17.4f : vinV < 17.0f;
  bool bypass = want && dcIn && lowBrick && !portBusy() && bypassMode == 0;
  if (bypass && !laptopBypass) { digitalWrite(PIN_LAPTOP_EN, LOW); delay(2); }
  laptopBypass = bypass;
  laptopOn = want && !bypass;
  digitalWrite(PIN_LAPTOP_BYP, laptopBypass ? HIGH : LOW);
  digitalWrite(PIN_LAPTOP_EN, laptopOn ? HIGH : LOW);
  laptopLimitPwm(laptopLimitA * LAPTOP_V_PER_A);
}

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static void inputTick() {
  bool dcIn = dcinV > 13.5f;
  usbDisabled = dcIn;
  digitalWrite(PIN_USB_DIS, usbDisabled ? HIGH : LOW);
}

// #region fan
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// Two side emitters on the board, then J13 for two more on the lid (WS2812B
// carriers on a wire). The lid pair mirrors the side pair.
static const int LED_COUNT = 4;
Adafruit_NeoPixel leds(LED_COUNT, PIN_LED_DATA, NEO_GRB + NEO_KHZ800);
static const uint32_t OFF = 0, RED = 0x400000, GREEN = 0x004000, BLUE = 0x000040, AMBER = 0x402000, WHITE = 0x303030;

static void ledTick(uint32_t now) {
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
void setup() {
  // Everything off before anything is measured.
  pinMode(PIN_BOOST_SD, OUTPUT); digitalWrite(PIN_BOOST_SD, HIGH);
  pinMode(PIN_PSE_EN, OUTPUT); digitalWrite(PIN_PSE_EN, LOW);
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
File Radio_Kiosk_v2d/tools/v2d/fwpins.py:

"""Write the MCU pin map (net -> LQFP-48 pin number) into firmware main.cpp.
Usage: fwpins.py pins.json main.cpp"""
import json, re, sys
PORT = {2: "PC13", 3: "PC14", 4: "PC15", 5: "PF0", 6: "PF1", **{10 + i: f"PA{i}" for i in range(8)},
        18: "PB0", 19: "PB1", 20: "PB2", 21: "PB10", 22: "PB11", 25: "PB12", 26: "PB13", 27: "PB14", 28: "PB15",
        29: "PA8", 30: "PA9", 31: "PA10", 32: "PA11", 33: "PA12", 34: "PA13", 37: "PA14", 38: "PA15",
        39: "PB3", 40: "PB4", 41: "PB5", 42: "PB6", 43: "PB7", 45: "PB8", 46: "PB9"}
CONST = {"LAPTOP_ILIM_PWM": "LAPTOP_ILIM"}
pins = json.load(open(sys.argv[1])); src = open(sys.argv[2]).read()
for net, pin in pins.items():
    port = PORT[int(pin)]
    if net in ("PD_SCL", "PD_SDA"):
        name = "PIN_SCL" if net == "PD_SCL" else "PIN_SDA"
        src, n = re.subn(rf"({name} = )P[A-F]\d+", rf"\g<1>{port}", src)
    else:
        name = "PIN_" + CONST.get(net, net)
        src, n = re.subn(rf"(static const int {name} = )P[A-F]\d+", rf"\g<1>{port}", src)
    if n != 1: sys.exit(f"{net}: {n} matches for {name}")
scl, sda = PORT[int(pins["PD_SCL"])], PORT[int(pins["PD_SDA"])]
src = re.sub(r"// #region bit-banged I2C on \S+ \(SCL\) / \S+ \(SDA\)", f"// #region bit-banged I2C on {scl} (SCL) / {sda} (SDA)", src)
open(sys.argv[2], "w").write(src)
print("firmware pins:", {n: PORT[int(p)] for n, p in pins.items()})
